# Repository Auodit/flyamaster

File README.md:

# 🚁 FLYAMASTER 飞控项目

> ⚠️ **版权警告 / COPYRIGHT WARNING** ⚠️
>
> **本项目受版权保护，严格保留所有权利！**
>
> 🚫 **禁止** 未经授权的复制、修改、分发、商用
> 🚫 **禁止** Fork、Clone、Download 本仓库
> 🚫 **禁止** 转载、引用本项目任何内容
>
> 违者将依法追究法律责任！详见 [LICENSE](LICENSE)
>
> ---
>
> **This project is protected by copyright. All rights strictly reserved!**
>
> 🚫 **PROHIBITED**: Unauthorized copying, modification, distribution, commercial use
> 🚫 **PROHIBITED**: Fork, Clone, Download this repository
> 🚫 **PROHIBITED**: Repost or cite any content from this project
>
> Violators will be prosecuted! See [LICENSE](LICENSE)

---

**项目名称**: FLYAMASTER - F405 Mini 高性能穿越机飞控
**版本**: v2.4.0
**最后更新**: 2026-01-23
**状态**: 🟢 开发中 (软件完成，硬件设计完成，等待验证)
**作者**: LI
**助手**: Doro *(Desktop Pet / 桌面宠物)*

---

## 📖 项目简介

FLYAMASTER 是一款基于 **STM32F405RGT6** 的高性能、开源、易扩展的四轴飞行控制器。

### 🌟 项目由来

> *"每个飞手心中都有一个造飞控的梦。"*

这个项目源于我对无人机的热爱。从第一次看到穿越机在空中翻滚、俯冲的那一刻起，我就被这种自由飞翔的感觉深深吸引。作为一名嵌入式开发者，我不满足于仅仅使用现成的飞控，而是想要**从零开始**，亲手打造一款属于自己的飞行控制器。

这不仅仅是一个技术项目，更是一段探索之旅——从最初的 Mahony 姿态解算调试，到 PID 参数的反复调优；从 DMA 通道冲突的抓狂，到最终看到四轴稳稳悬停的那一刻的成就感。每一行代码、每一条 PCB 走线，都凝聚着对飞行的热爱和对技术的追求。

**FLYAMASTER** = **FLY** (飞行) + **A** (一个) + **MASTER** (大师) —— 愿每一位使用者都能成为飞行大师！

### 🎯 多固件支持

本硬件设计兼容多种主流开源飞控固件：

| 固件 | 适用场景 | 支持状态 |
|------|----------|----------|
| **INAV** | 固定翼 / 长航时无人机 / GPS 导航 | ✅ 完全兼容 |
| **Betaflight** | 穿越机 / 竞速无人机 / 花飞 | ✅ 完全兼容 |
| **ArduPilot** | 专业航拍 / 测绘 / 自主任务 | ✅ 完全兼容 |
| **FLYAMASTER (自研)** | 学习研究 / 定制开发 | ✅ 原生支持 |

> 💡 **提示**: 硬件引脚分配遵循 Betaflight 标准，可直接使用 Betaflight Configurator 进行配置。
> 对于 INAV 和 ArduPilot，需要创建对应的 Target 定义文件。

### 核心特性

- **高性能 MCU**: STM32F405RGT6 (168MHz, 1MB Flash, 192KB RAM)
- **多固件兼容**: 支持 INAV / Betaflight / ArduPilot / 自研固件
- **宽电压输入**: 支持 **2S-9S 电池** (4.5V-40V)，兼容各类电调
- **板载 OSD**: AT7456E 视频叠加芯片，实时显示飞行数据
- **实时操作系统**: FreeRTOS CMSIS_V2 (自研固件)
- **姿态解算**: Mahony 互补滤波 (500Hz)
- **控制算法**: 串级 PID (角度环 + 角速度环)
- **传感器融合**: IMU + 气压计 + 磁力计 + GPS + 光流
- **遥控接收**: ELRS/CRSF 协议 (420kbps, 双向遥测)
- **黑匣子**: W25Q128 Flash 日志记录 (16MB)
- **状态指示**: 7 颗专业级 LED 飞行仪表盘
- **USB 反灌保护**: 肖特基二极管隔离，安全可靠

### 设计哲学

1. **控制回路隔离**: 姿态解算与 PID 控制拥有最高优先级
2. **DMA 满载策略**: 所有高吞吐量接口强制开启 DMA
3. **资源冲突零容忍**: 针对 F405 的 DMA 通道冲突采用硬件重映射方案

---

## 🧠 核心算法原理

### 姿态解算 - Mahony 互补滤波

飞控的"大脑"是姿态解算算法。我们采用 **Mahony 互补滤波器**，它巧妙地融合了陀螺仪和加速度计的数据：

```
                    ┌─────────────────────────────────────────┐
                    │         Mahony 互补滤波器               │
                    └─────────────────────────────────────────┘
                    
    陀螺仪 (高频响应)                      加速度计 (低频稳定)
         │                                      │
         ▼                                      ▼
    ┌─────────┐                           ┌─────────┐
    │ 角速度  │                           │ 重力向量│
    │ ω       │                           │ a       │
    └────┬────┘                           └────┬────┘
         │                                      │
         │    ┌──────────────────────────┐     │
         └───►│  四元数微分方程积分       │◄────┘
              │  q̇ = ½ q ⊗ ω_corrected   │
              └───────────┬──────────────┘
                          │
                          ▼
                    ┌─────────┐
                    │ 四元数 q │ ──► Roll, Pitch, Yaw
                    └─────────┘
```

**核心公式**:
- 误差估计: `e = a × v` (加速度计测量值与估计重力方向的叉积)
- PI 校正: `ω_corrected = ω_gyro + Kp·e + Ki·∫e·dt`
- 四元数更新: `q += ½·q⊗ω·dt`

### 串级 PID 控制

采用**角度环 + 角速度环**的串级结构，外环输出作为内环的设定值：

```
    目标角度 ──┬──► [角度环 PID] ──► 目标角速度 ──┬──► [角速度环 PID] ──► 电机输出
               │                                  │
    当前角度 ──┘                    当前角速度 ──┘
```

**为什么用串级？**
- 外环 (角度环): 响应慢但稳定，负责"往哪飞"
- 内环 (角速度环): 响应快，负责"怎么飞"
- 两环配合，既稳定又灵敏

### 电机混控 - Airmode 算法

X 型机架的混控公式：
```
M1 (右前) = Throttle - Roll - Pitch - Yaw
M2 (左后) = Throttle + Roll + Pitch - Yaw
M3 (左前) = Throttle + Roll - Pitch + Yaw
M4 (右后) = Throttle - Roll + Pitch + Yaw
```

**Airmode 的精髓**: 当电机输出超限时，整体平移油门中心，保证姿态控制差分不变——"姿态优先，油门让步"。

---

## ⚡ 电路设计亮点

### 宽电压电源架构 (2S-9S)

```
    电池 (4.5-40V) ──► SY8303 DCDC ──► 5V/3A ──► RT9193 LDO ──► 3.3V/500mA
         │                  │                         │
         │                  ├──► USB 5V (带反灌保护)   ├──► MCU
         │                  ├──► 蜂鸣器               ├──► 传感器
         │                  └──► 外设接口             └──► Flash/OSD
         │
         ├──► 电机 (直接电池供电)
         └──► ADC 电压检测 (1:11 分压)
```

**为什么选 SY8303？**
- 输入范围 4.5-40V，覆盖 2S-9S 电池
- 效率高达 95%，发热小
- SOT-23-6 封装，体积小巧
- 价格仅 ¥0.8，性价比极高

### USB 反灌保护

**问题**: 电池供电时，5V 会通过 USB 反灌到电脑，导致 MCU 误判 USB 已连接。

**解决方案**: 肖特基二极管 (SS14) 隔离 + PB9 检测引脚

```
    USB VBUS ──┬──[SS14 二极管]──► +5V_USB
               │
               └──[10kΩ]──► PB9 (USB_DETECT, Pull-down)
```

### 7 颗 LED 专业飞行仪表盘

| 分组 | LED | 颜色 | 功能 |
|:---|:---|:---|:---|
| 核心系统 | LED_SYS | 蓝 | 系统心跳 (闪烁=待机, 常亮=已解锁) |
| 核心系统 | LED_ERR | 红 | 警告/错误 (快闪=传感器故障) |
| 导航链路 | LED_GPS | 绿 | GPS 状态 (闪烁=搜星, 常亮=3D Fix) |
| 导航链路 | LED_RX | 黄 | 遥控信号 (常亮=正常, 灭=Failsafe) |
| 飞行任务 | LED_MODE | 白 | 飞行模式指示 |
| 飞行任务 | LED_LOG | 橙 | 黑匣子记录状态 |
| 飞行任务 | LED_VTX | 青 | 图传状态 |

---

## 🔧 问题发现与解决

开发过程中遇到了不少"坑"，这里记录一些典型问题和解决方案：

### 问题 1: DMA 通道冲突

**现象**: WS2812 RGB 灯和 SBUS 接收机同时工作时，数据错乱。

**原因**: STM32F4 的 DMA 通道是硬件绑定的，TIM3_CH4 和 UART4_RX 共用 DMA1_Stream2。

**解决**: 将 WS2812 从 TIM3_CH4 (PB1) 迁移到 TIM1_CH1 (PA8)，使用 DMA2 通道，彻底隔离。

### 问题 2: I2C 总线竞争

**现象**: 多任务环境下，MPU6050 和 SPL06 偶发读取失败。

**原因**: 两个任务同时访问 I2C1 总线，导致冲突。

**解决**: 引入 FreeRTOS 互斥锁 (`i2c1MutexHandle`)，所有 I2C 操作前加锁，操作后解锁。

### 问题 3: Failsafe 油门被覆盖 (严重!)

**现象**: 失控保护触发后，飞机不下降反而继续按遥控器油门飞行。

**原因**: 代码中先设置 `throttle = FAILSAFE_DESCENT_THROTTLE`，后又被 `throttle = SBUS_GetThrottle()` 覆盖。

**解决**: 在读取遥控器油门前检查 Failsafe 状态，Failsafe 期间跳过遥控器输入。

### 问题 4: 偏航角漂移

**现象**: 飞机静止时，Yaw 角缓慢漂移。

**原因**: 仅使用 6 轴 IMU (加速度计+陀螺仪)，无法校正偏航。

**解决**: 集成 QMC5883L 磁力计，升级为 9 轴 AHRS，利用地磁场校正偏航。

### 问题 5: 高频 printf 导致控制抖动

**现象**: 在 500Hz 的 IMU 任务中加 printf 调试，飞机开始抖动。

**原因**: printf 是阻塞式的，每次调用耗时 1-2ms，严重影响控制回路。

**解决**: 开发 RingBuffer 异步日志系统，`Log_Printf()` 仅需 <10us，数据通过 DMA 后台发送。

---

## 🛠️ 技术栈

| 类别 | 技术选型 | 说明 |
|------|----------|------|
| **MCU** | STM32F405RGT6 | ARM Cortex-M4F @ 168MHz |
| **RTOS** | FreeRTOS | CMSIS_V2 接口 |
| **IDE** | Keil MDK-ARM | ARM Compiler 6 |
| **配置工具** | STM32CubeMX | HAL 库生成 |
| **EDA** | KiCad 9.0 | PCB 设计 |
| **调试** | 匿名上位机 V7 | 实时数据可视化 |

---

## 📐 硬件设计

### PCB 渲染图

| 正面 (Top) | 反面 (Bottom) |
|:---:|:---:|
|  |  |

### 原理图

📄 **原理图 PDF**: [Hardware/zero star/zero star.pdf](Hardware/zero%20star/zero%20star.pdf)

### 主要芯片

| 芯片 | 功能 | 接口 |
|------|------|------|
| STM32F405RGT6 | 主控 MCU | - |
| MPU6050 | 6轴 IMU | I2C1 (0x68) |
| SPL06-001 | 气压计 | I2C1 (0x76) |
| QMC5883L | 磁力计 | I2C1 (0x0D) |
| W25Q128 | 16MB Flash | SPI1 |
| AT7456E | OSD 视频叠加 | SPI1 |
| SY8303 | DCDC 5V/3A (2S-9S 输入) | - |
| RT9193-33 | LDO 3.3V/500mA | - |

### 接口定义

| 接口 | 引脚 | 功能 | 波特率 |
|------|------|------|--------|
| J1 | USB-C | 固件升级/调参 | CDC |
| J2 | PA2/PA3 | GPS 模块 | 115200 |
| J3 | PA9/PA10 | K210 上位机 | 921600 |
| J4 | PC6-PC9 | 4-in-1 ESC | PWM 400Hz |
| J5 | PC12/PD2 | 光流模块 | 115200 |
| J6 | PC10/PC11 | VTX SmartAudio | 115200  |
| J22 | PB10/PB11 | ELRS 接收机 | 420000 (CRSF) |

---

## 📚 文档索引

| 编号 | 文档名称 | 说明 | 链接 |
|------|----------|------|------|
| 00 | README.md | 项目总览与索引 (本文档) | - |
| 01 | 01_definitions.md | 命名规范与接口定义 | [查看](plans/01_definitions.md) |
| 02 | 02_project_roadmap.md | 项目路线图与待办事项 | [查看](plans/02_project_roadmap.md) |
| 03 | 03_issue_tracker.md | 问题追踪日志 (Bug/Risk) | [查看](plans/03_issue_tracker.md) |
| 04 | 04_algo_design.md | 算法设计与优化记录 | [查看](plans/04_algo_design.md) |
| 05 | 05_changelog.md | 版本更新日志 | [查看](plans/05_changelog.md) |
| 06 | 06_operation_guide.md | 操作指南与环境搭建 | [查看](plans/06_operation_guide.md) |
| 07 | 07_research_and_ideas.md | 调研分析与创意池 | [查看](plans/07_research_and_ideas.md) |
| 08 | 08_hardware_design.md | 硬件架构与 PCB 设计 | [查看](plans/08_hardware_design.md) |

---

## 🚀 快速开始

### 1. 环境准备

```bash
# 必需软件
- Keil MDK-ARM v5.38+
- STM32CubeMX v6.10+
- ST-Link 驱动
```

### 2. 编译项目

1. 打开 `FLYAMASTER/MDK-ARM/FLYAMASTER.uvprojx`
2. 点击 `Build` (F7) 编译
3. 点击 `Download` (F8) 烧录

### 3. 调试连接

- **SWD 接口**: PA13 (SWDIO), PA14 (SWCLK)
- **USB 虚拟串口**: PA11/PA12 (CDC)
- **匿名上位机**: USART1 (PA9/PA10) @ 921600 baud

---

## 📁 目录结构

```
FLYAMASTER/
├── 3D/                      # 3D 模型文件
├── FLYAMASTER/              # 固件源代码
│   ├── Core/
│   │   ├── Inc/             # 头文件
│   │   │   ├── mpu6050.h    # IMU 驱动
│   │   │   ├── mahony.h     # 姿态解算
│   │   │   ├── pid.h        # PID 控制器
│   │   │   ├── motor.h      # 电机混控
│   │   │   ├── sbus.h       # CRSF 接收
│   │   │   ├── gps.h        # GPS 解析
│   │   │   ├── at7456e.h    # OSD 驱动
│   │   │   └── ...
│   │   └── Src/             # 源文件
│   │       ├── freertos.c   # RTOS 任务
│   │       ├── mpu6050.c    # IMU 驱动实现
│   │       ├── mahony.c     # Mahony 滤波
│   │       ├── pid.c        # PID 算法
│   │       ├── motor.c      # 电机控制
│   │       └── ...
│   └── MDK-ARM/             # Keil 工程
│       ├── FLYAMASTER.uvprojx
│       └── ...
├── Hardware/                # 硬件设计
│   └── zero star/           # KiCad 工程
│       ├── zero star.kicad_sch    # 原理图
│       ├── zero star.kicad_pcb    # PCB
│       └── zero star.pdf          # 原理图 PDF
├── plans/                   # 项目文档
│   ├── README.md            # 文档索引
│   ├── 01_definitions.md    # 接口定义
│   ├── 02_project_roadmap.md # 路线图
│   ├── 03_issue_tracker.md  # 问题追踪
│   ├── 04_algo_design.md    # 算法设计
│   ├── 05_changelog.md      # 更新日志
│   ├── 06_operation_guide.md # 操作指南
│   ├── 07_research_and_ideas.md # 调研分析
│   ├── 08_hardware_design.md # 硬件设计
│   └── archive/             # 废弃文档归档
├── .gitignore               # Git 忽略规则
└── LICENSE                  # 版权声明
```

---

## 🎯 项目状态

### ✅ 已完成

- [x] 硬件驱动 (IMU, PWM, CRSF, GPS, OSD)
- [x] 姿态解算 (Mahony 互补滤波)
- [x] 姿态控制 (串级 PID)
- [x] 定高控制 (气压计 PID)
- [x] GPS 定点 (位置环 PID)
- [x] OSD 显示 (AT7456E)
- [x] 匿名上位机协议 (V7)
- [x] 硬件原理图设计 (KiCad)
- [x] 7 颗 LED 状态指示系统
- [x] USB 插入检测 (反灌保护)

### 🚧 进行中

- [ ] PCB 布局优化
- [ ] 打样验证

### 📋 计划中

- [ ] EKF 状态估计 (可选)
- [ ] 航点飞行
- [ ] 自动返航 (RTH)

---

## 👥 贡献者

- **LI** - 项目作者 & 核心开发者
- **Doro** *(Desktop Pet / 桌面宠物)* - AI 助手 & 文档撰写

---

## ⚖️ 版权声明

```
================================================================================
                    FLYAMASTER 飞控项目 - 版权声明
================================================================================

版权所有 (C) 2026 FLYAMASTER 项目组
Copyright (C) 2026 FLYAMASTER Project Team

                       严格保留所有权利
                  ALL RIGHTS STRICTLY RESERVED

未经版权所有者明确书面授权，严禁：
1. 复制、下载、存储本项目的任何部分
2. 修改、改编、翻译本项目的任何内容
3. 分发、传播、共享本项目的任何文件
4. 将本项目用于任何商业目的
5. 基于本项目创建衍生作品
6. 对本项目进行逆向工程
7. 在任何平台转载、引用本项目内容

任何未经授权的使用将被视为侵权，版权所有者保留追究法律责任的权利。

详见 LICENSE 文件
================================================================================
```

---

## 🙏 致谢

感谢开源社区的前辈们，特别是：
- **Betaflight** / **INAV** / **ArduPilot** 项目，提供了宝贵的参考
- **Mahony** 和 **Madgwick** 的姿态解算算法论文
- **立创开源硬件平台**，提供了电源方案参考
- 所有在 GitHub Issues 中提供反馈的朋友们

---

**文档版本**: v2.4.0
**最后更新**: 2026-01-23
**作者**: LI | **助手**: Doro

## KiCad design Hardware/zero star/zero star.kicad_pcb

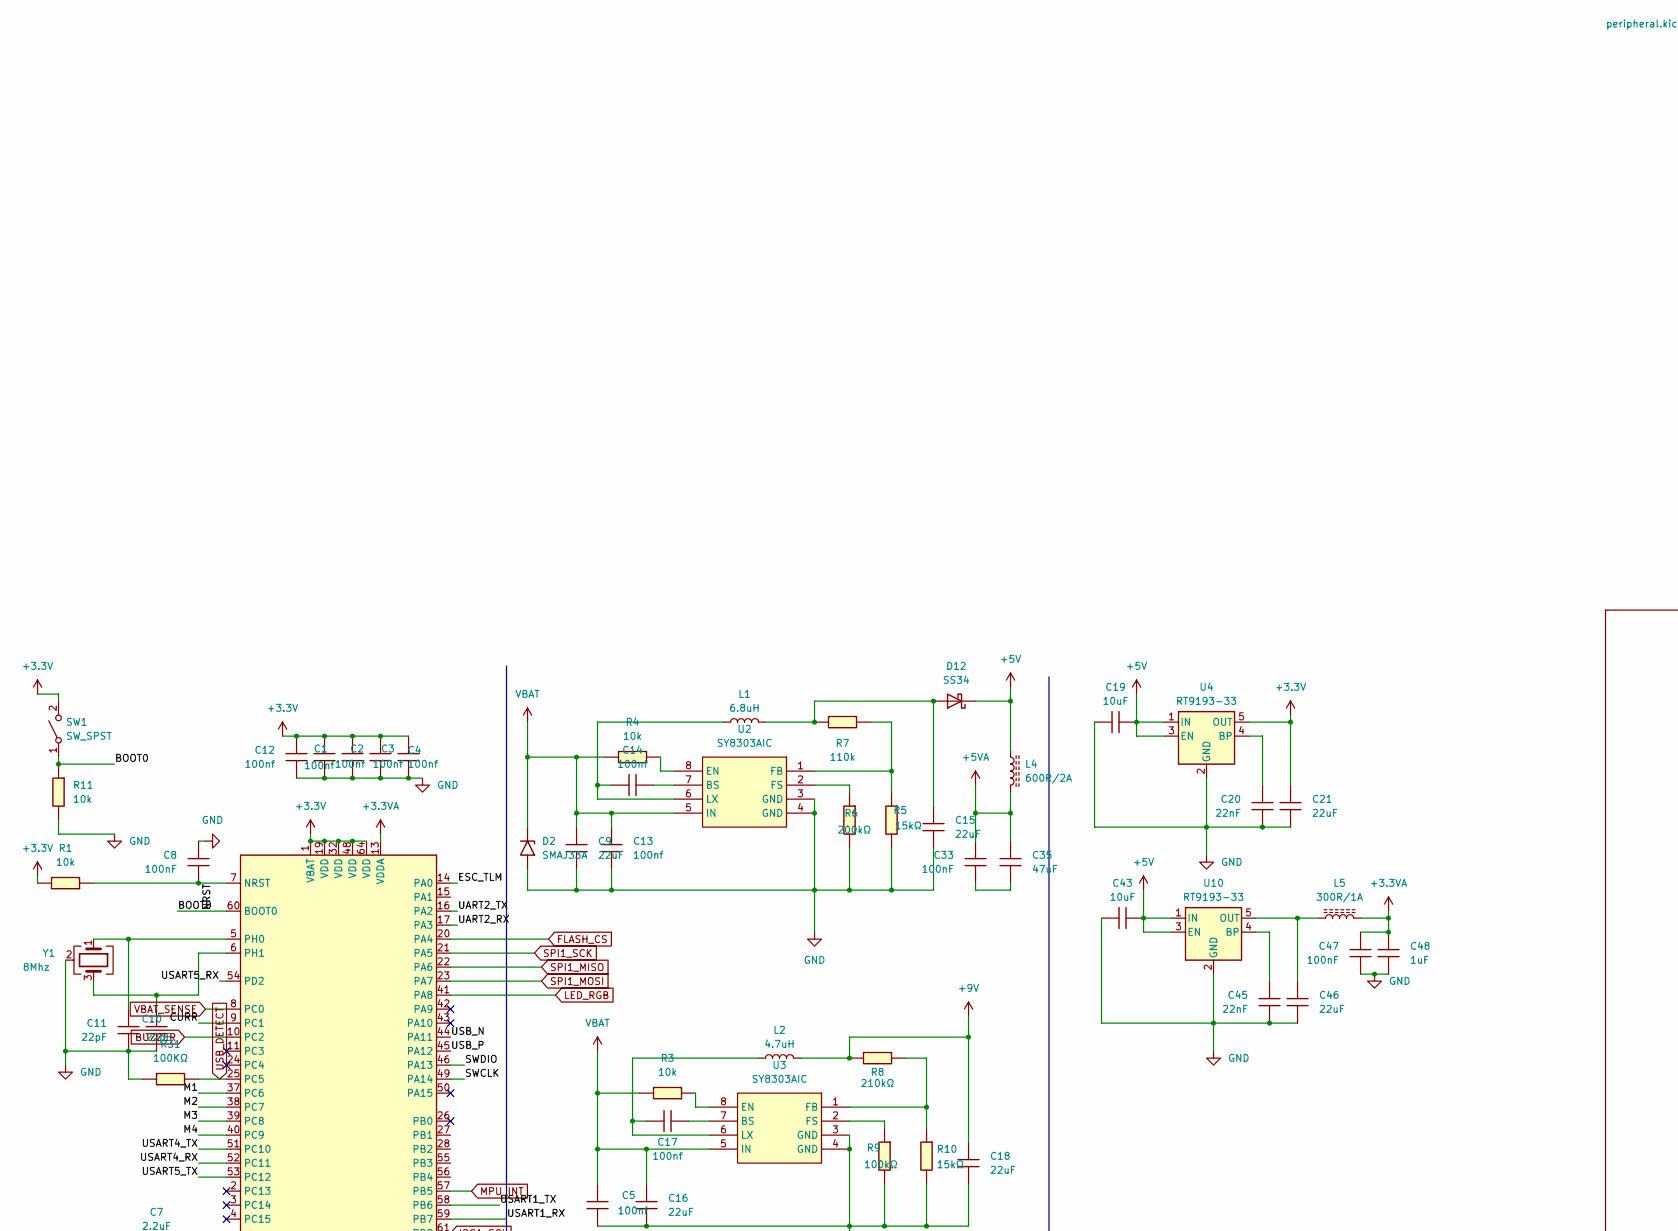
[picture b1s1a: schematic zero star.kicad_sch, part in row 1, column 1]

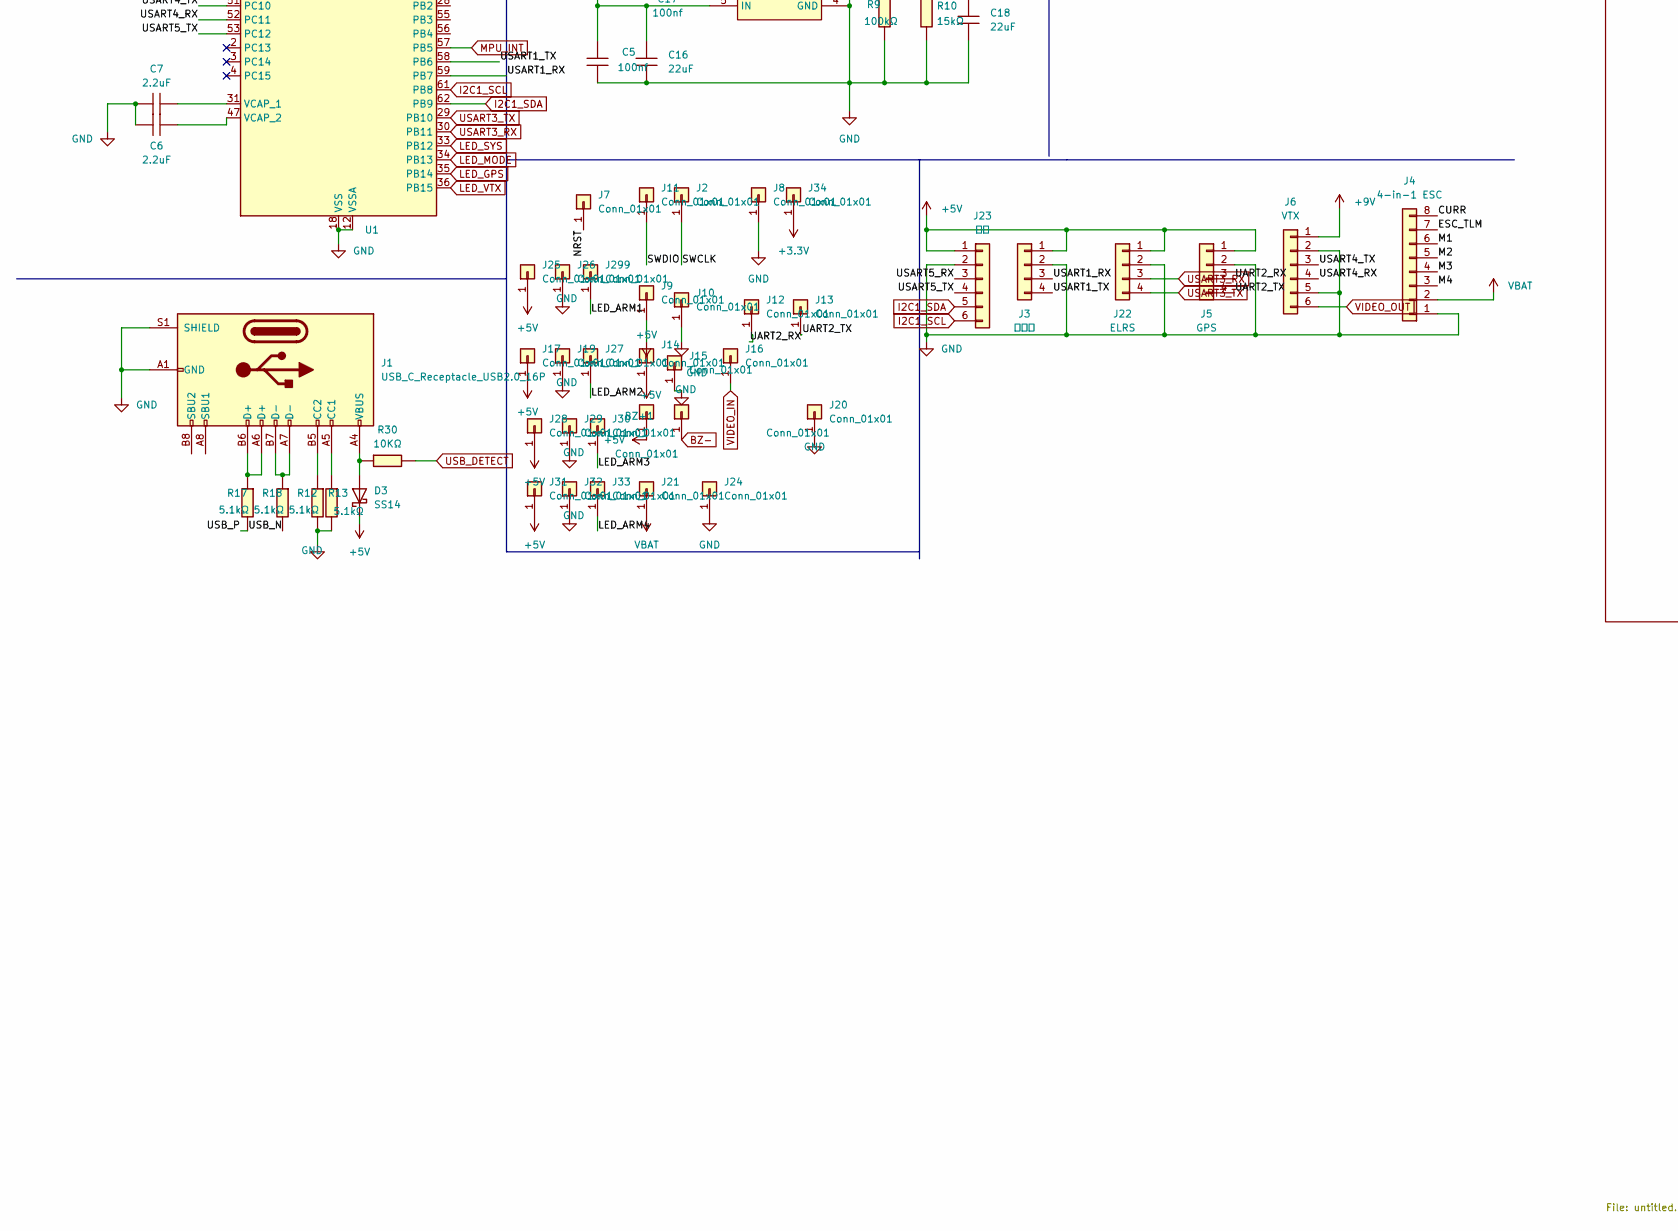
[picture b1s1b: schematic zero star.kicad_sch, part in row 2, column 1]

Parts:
BZ+1: Conn_01x01; SolderWirePad_1x01_SMD_1x2mm
C1, C2, C3, C4, C12, C13, C14, C16, C17: 100nf; C_0603
C5, C9, C15, C18, C21, C46: 22uF; C_0603
C6, C7: 2.2uF; C_0603
C8, C33, C47: 100nF; C_0603
C10, C11: 22pF; C_0603
C19, C43: 10uF; C_0603
C20, C45: 22nF; C_0603
C35: 47uF; C_0603
C48: 1uF; C_0603
D2: SMAJ33A; D_SMA
D3: SS14; D_SMA
D12: SS34; D_SOD-123
J1: USB_C_Receptacle_USB2.0_16P; USB_C_Receptacle_HRO_TYPE-C-31-M-12
J2, J7, J8, J9, J10, J11, J12, J13, J14, J15, J16, J17, J18, J19, J20, J21, J24, J25, J26, J27, J28, J29, J30, J31, J32, J33, J34, J299: Conn_01x01; SolderWirePad_1x01_SMD_1x2mm
J3: 上位机; JST_SH_SM04B-SRSS-TB_1x04-1MP_P1.00mm_Horizontal; Part Number 1-0401FBV0T
J4: 4-in-1 ESC; JST_SH_SM08B-SRSS-TB_1x08-1MP_P1.00mm_Horizontal
J5: GPS; JST_SH_SM04B-SRSS-TB_1x04-1MP_P1.00mm_Horizontal; Part Number 1-0401FBV0T
J6: VTX; JST_SH_SM06B-SRSS-TB_1x06-1MP_P1.00mm_Horizontal; Part Number 1-0601FBV0T
J22: ELRS; JST_SH_SM04B-SRSS-TB_1x04-1MP_P1.00mm_Horizontal; Part Number 1-0401FBV0T
J23: 光流; JST_SH_SM06B-SRSS-TB_1x06-1MP_P1.00mm_Horizontal; Part Number 1-0601FBV0T
L1: 6.8uH; L_Bourns-SRN4018
L2: 4.7uH; L_Bourns-SRN4018
L4: 600R/2A; L_0805_2012Metric_Pad1.05x1.20mm_HandSolder
L5: 300R/1A; L_0805_2012Metric_Pad1.05x1.20mm_HandSolder
R1, R3, R4, R11: 10k; R_0603
R5, R10: 15kΩ; R_0603
R6: 200kΩ; R_0603
R7: 110k; R_0603
R8: 210kΩ; R_0603
R9: 100kΩ; R_0603
R12, R13, R17, R18: 5.1kΩ; R_0603
R30: 10KΩ; R_0603
R31: 100KΩ; R_0603
SW1: SW_SPST; SW_SPST_B3U-3000P-B
U1: STM32F405RGTx; LQFP-64_10x10mm_P0.5mm
U2, U3: SY8303AIC; TSOT-23-8; LCSC Part C97054
U4, U10: RT9193-33; SOT-23-5
Y1: 8Mhz; Crystal_SMD_3225-4Pin_3.2x2.5mm

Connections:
+3.3V: C1.1, C2.1, C3.1, C4.1, C12.1, C21.1, J34.1, R1.1, SW1.2 (B), U1.1 (VBAT), U1.19 (VDD), U1.32 (VDD), U1.48 (VDD), U1.64 (VDD), U4.5 (OUT); also elsewhere on the board
+3.3VA: C47.1, C48.1, L5.2, U1.13 (VDDA); also elsewhere on the board
+5V: BZ+1.1, C19.1, C43.1, D3.1 (K), D12.1 (K), J3.1, J5.1, J9.1, J14.1, J17.1, J22.1, J23.1, J25.1, J28.1, J31.1, L4.1, U4.1 (IN), U4.3 (EN), U10.1 (IN), U10.3 (EN); also elsewhere on the board
+5VA: C33.1, C35.1, L4.2; also elsewhere on the board
+9V: C18.1, J6.1, L2.2, R8.2
/BOOT0: R11.2, SW1.1 (A), U1.60 (BOOT0)
/LED_ARM1: J299.1
/LED_ARM2: J27.1
/LED_ARM3: J30.1
/LED_ARM4: J33.1
/M1: J4.6, U1.37 (PC6)
/M2: J4.5, U1.38 (PC7)
/M3: J4.4, U1.39 (PC8)
/M4: J4.3, U1.40 (PC9)
/NRST: C8.2, J7.1, R1.2, U1.7 (NRST)
/SWCLK: J2.1, U1.49 (PA14)
/SWDIO: J11.1, U1.46 (PA13)
/UART2_RX: J5.3, J12.1, U1.17 (PA3)
/UART2_TX: J5.4, J13.1, U1.16 (PA2)
/USART1_RX: J3.3, U1.59 (PB7)
/USART1_TX: J3.4, U1.58 (PB6)
/USART4_RX: J6.4, U1.52 (PC11)
/USART4_TX: J6.3, U1.51 (PC10)
/USART5_RX: J23.3, U1.54 (PD2)
/USART5_TX: J23.4, U1.53 (PC12)
/USB_N: R18.1, U1.44 (PA11)
/USB_P: R17.1, U1.45 (PA12)
BUZZER: U1.10 (PC2); also elsewhere on the board
BZ-: J18.1; also elsewhere on the board
FLASH_CS: U1.24 (PC4); also elsewhere on the board
I2C1_SCL: J23.6, U1.61 (PB8); also elsewhere on the board
I2C1_SDA: J23.5, U1.62 (PB9); also elsewhere on the board
LED_GPS: U1.35 (PB14); also elsewhere on the board
LED_MODE: U1.34 (PB13); also elsewhere on the board
LED_RGB: U1.41 (PA8)
LED_SYS: U1.33 (PB12); also elsewhere on the board
LED_VTX: U1.36 (PB15); also elsewhere on the board
MPU_INT: U1.57 (PB5); also elsewhere on the board
unnamed: D3.2 (A), J1.A4 (VBUS), J1.A9 (VBUS), J1.B4 (VBUS), J1.B9 (VBUS), R30.2
unnamed: C15.1, D12.2 (A), L1.2, R7.2
unnamed: J1.A5 (CC1), R13.2
unnamed: J1.A6 (D+), J1.B6 (D+), R17.2
unnamed: J1.A7 (D-), J1.B7 (D-), R18.2
unnamed: J1.B5 (CC2), R12.2
unnamed: C11.1, U1.5 (PH0), Y1.1
unnamed: C10.1, U1.6 (PH1), Y1.3
unnamed: C7.1, U1.31 (VCAP_1)
unnamed: C6.1, U1.47 (VCAP_2)
unnamed: C14.2, U2.7 (BS)
unnamed: R4.2, U2.8 (EN)
unnamed: R5.2, R7.1, U2.1 (FB)
unnamed: R6.2, U2.2 (FS)
unnamed: C14.1, L1.1, U2.6 (LX)
unnamed: C17.2, U3.7 (BS)
unnamed: R3.2, U3.8 (EN)
unnamed: R8.1, R10.2, U3.1 (FB)
unnamed: R9.2, U3.2 (FS)
unnamed: C17.1, L2.1, U3.6 (LX)
unnamed: C20.1, U4.4 (BP)
unnamed: C45.1, U10.4 (BP)
unnamed: C46.1, L5.1, U10.5 (OUT)
SPI1_MISO: U1.22 (PA6); also elsewhere on the board
SPI1_MOSI: U1.23 (PA7); also elsewhere on the board
SPI1_SCK: U1.21 (PA5); also elsewhere on the board
USART3_RX: J22.3, U1.30 (PB11)
USART3_TX: J22.4, U1.29 (PB10)
USB_DETECT: R30.1, R31.1, U1.25 (PC5)
VBAT: C5.1, C9.1, C13.1, C16.1, D2.1 (A1), J4.2, J21.1, R3.1, R4.1, U2.5 (IN), U3.5 (IN); also elsewhere on the board
VBAT_SENSE: U1.8 (PC0); also elsewhere on the board
VIDEO_IN: J16.1; also elsewhere on the board
VIDEO_OUT: J6.6; also elsewhere on the board

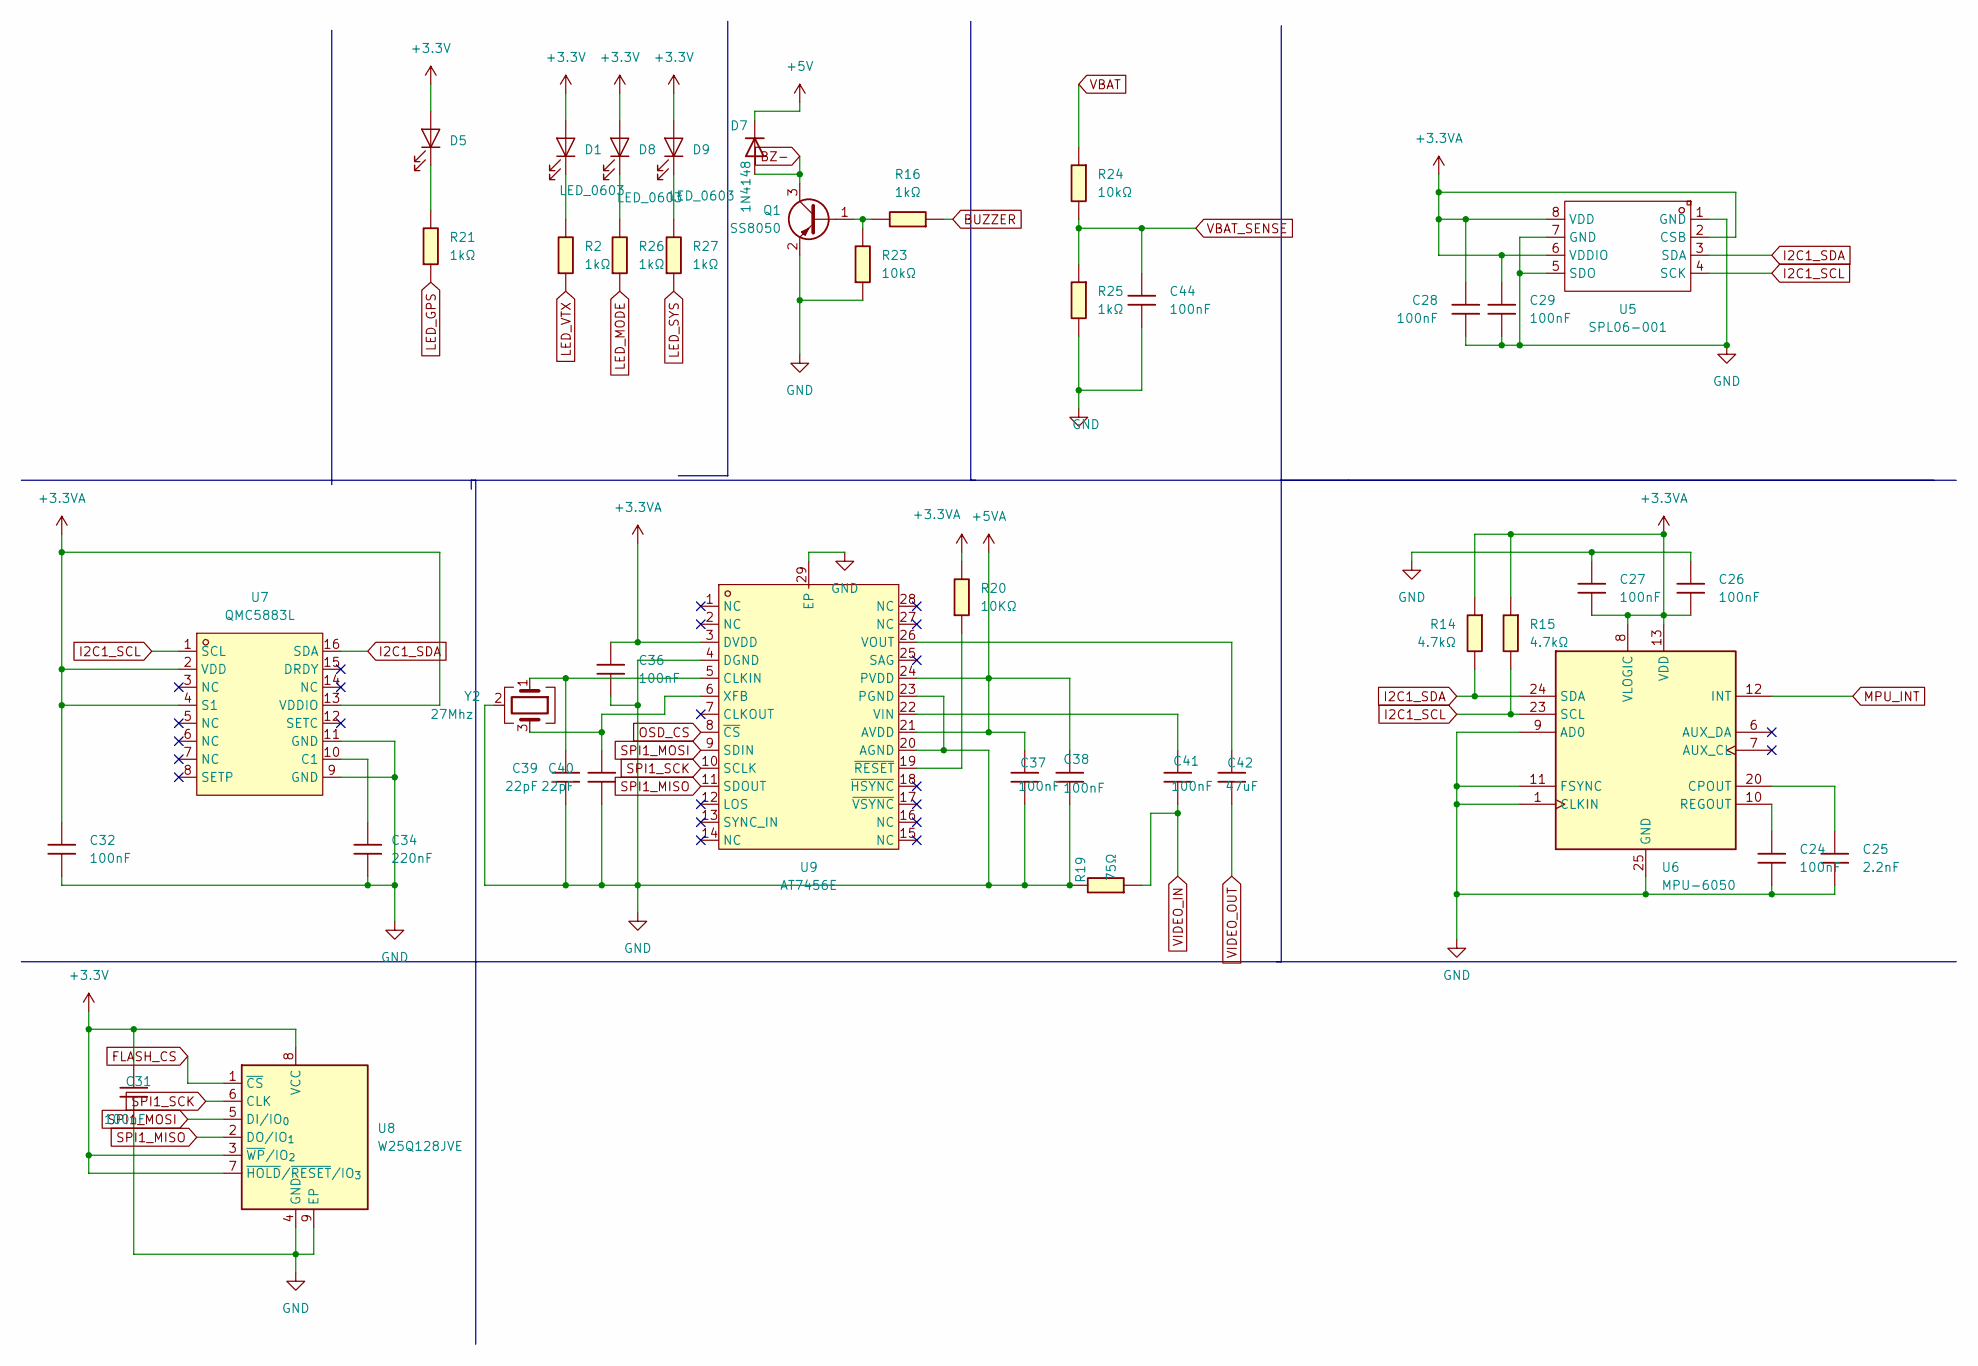
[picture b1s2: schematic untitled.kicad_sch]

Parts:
C24, C26, C27, C28, C29, C31, C32, C36, C37, C38, C41, C44: 100nF; C_0603
C25: 2.2nF; C_0603
C34: 220nF; C_0603
C39, C40: 22pF; C_0603
C42: 47uF; C_0603
D1, D5, D8, D9: LED_0603
D7: 1N4148; D_SOD-123
Q1: SS8050; SOT-23
R2, R16, R21, R25, R26, R27: 1kΩ; R_0603
R14, R15: 4.7kΩ; R_0603
R19: 75Ω; R_0603
R20: 10KΩ; R_0603
R23, R24: 10kΩ; R_0603
U5: SPL06-001; SENSOR-SMD_SPL06-001; LCSC Part C2684428
U6: MPU-6050; QFN-24-1EP_4x4mm_P0.5mm_EP2.6x2.6mm_ThermalVias
U7: QMC5883L; LGA-16_L3.0-W3.0-P0.50-BL_SQ; LCSC Part C976032
U8: W25Q128JVE; WSON-8-1EP_8x6mm_P1.27mm_EP3.4x4.3mm
U9: AT7456E; TSSOP-28_L9.7-W4.4-P0.65-LS6.4-BL-EP-2; LCSC Part C82351
Y2: 27Mhz; Crystal_SMD_3225-4Pin_3.2x2.5mm

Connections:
+3.3V: C31.1, D1.2 (A), D5.2 (A), D8.2 (A), D9.2 (A), U8.3 (~WP/IO_{2}), U8.7 (~HOLD/~RESET/IO_{3}), U8.8 (VCC); also elsewhere on the board
+3.3VA: C26.2, C27.2, C28.1, C29.1, C32.1, C36.1, R14.2, R15.2, R20.1, U5.2 (CSB), U5.6 (VDDIO), U5.8 (VDD), U6.8 (VLOGIC), U6.13 (VDD), U7.2 (VDD), U7.4 (S1), U7.13 (VDDIO), U9.3 (DVDD); also elsewhere on the board
+5V: D7.1 (K); also elsewhere on the board
+5VA: C37.1, C38.1, U9.21 (AVDD), U9.24 (PVDD); also elsewhere on the board
BUZZER: R16.2; also elsewhere on the board
BZ-: D7.2 (A), Q1.3 (C); also elsewhere on the board
FLASH_CS: U8.1 (~CS); also elsewhere on the board
I2C1_SCL: R15.1, U5.4 (SCK), U6.23 (SCL), U7.1 (SCL); also elsewhere on the board
I2C1_SDA: R14.1, U5.3 (SDA), U6.24 (SDA), U7.16 (SDA); also elsewhere on the board
LED_GPS: R21.2; also elsewhere on the board
LED_MODE: R26.2; also elsewhere on the board
LED_SYS: R27.2; also elsewhere on the board
LED_VTX: R2.2; also elsewhere on the board
MPU_INT: U6.12 (INT); also elsewhere on the board
unnamed: D1.1 (K), R2.1
unnamed: D5.1 (K), R21.1
unnamed: D8.1 (K), R26.1
unnamed: D9.1 (K), R27.1
unnamed: Q1.1 (B), R16.1, R23.1
unnamed: C25.1, U6.20 (CPOUT)
unnamed: C24.1, U6.10 (REGOUT)
unnamed: C34.1, U7.10 (C1)
unnamed: C39.1, U9.5 (CLKIN), Y2.1
unnamed: C41.1, U9.22 (VIN)
unnamed: C42.1, U9.26 (VOUT)
unnamed: C40.1, U9.6 (XFB), Y2.3
unnamed: R20.2, U9.19 (~RESET)
SPI1_MISO: U8.2 (DO/IO_{1}), U9.11 (SDOUT); also elsewhere on the board
SPI1_MOSI: U8.5 (DI/IO_{0}), U9.9 (SDIN); also elsewhere on the board
SPI1_SCK: U8.6 (CLK), U9.10 (SCLK); also elsewhere on the board
VBAT: R24.2; also elsewhere on the board
VBAT_SENSE: C44.1, R24.1, R25.2; also elsewhere on the board
VIDEO_IN: C41.2, R19.2; also elsewhere on the board
VIDEO_OUT: C42.2; also elsewhere on the board

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
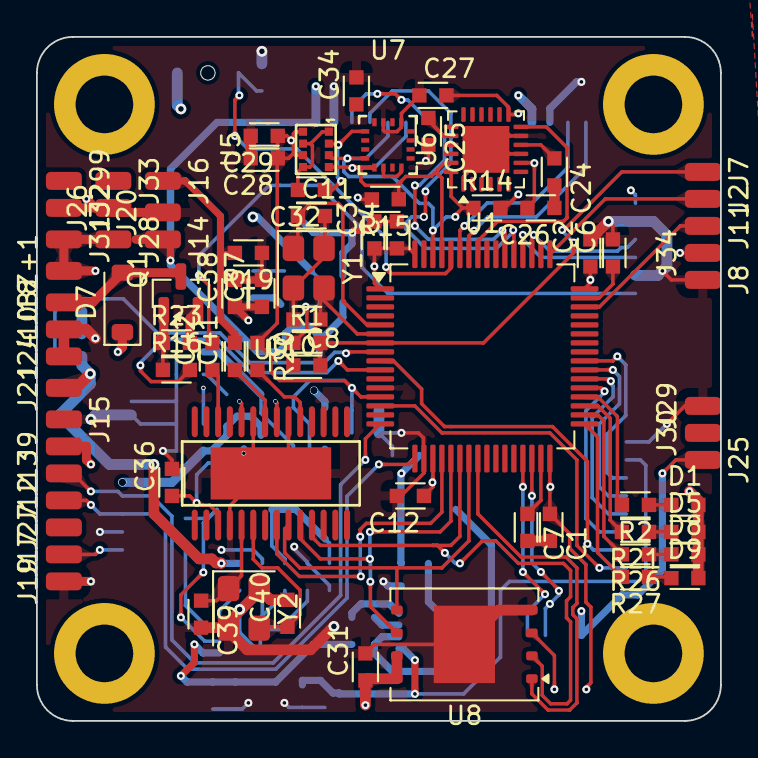
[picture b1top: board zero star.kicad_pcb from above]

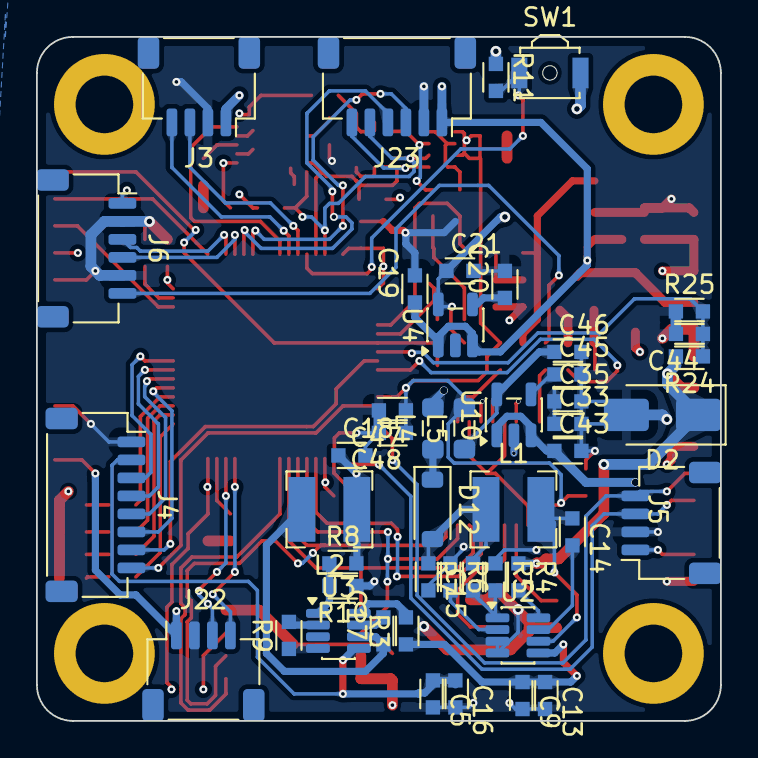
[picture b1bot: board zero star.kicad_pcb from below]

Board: 4 copper layers, 38.0 x 38.0 mm, 127 parts (47 on the bottom side), 75 nets.

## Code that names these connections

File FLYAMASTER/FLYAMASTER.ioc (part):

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Mcu.Name=STM32F405RGTx
Mcu.Package=LQFP64
Mcu.UserName=STM32F405RGTx
PA0-WKUP.GPIOParameters=GPIO_PuPd,GPIO_Label
PA0-WKUP.GPIO_Label=Power_Key
PA0-WKUP.GPIO_PuPd=GPIO_PULLDOWN
PA0-WKUP.Signal=GPIO_Input
PA11.Mode=Device_Only
PA11.Signal=USB_OTG_FS_DM
PA12.Mode=Device_Only
PA12.Signal=USB_OTG_FS_DP
PA13.Mode=Serial_Wire
PA13.Signal=SYS_JTMS-SWDIO
PA14.Mode=Serial_Wire
PA14.Signal=SYS_JTCK-SWCLK
PA2.Mode=Asynchronous
PA2.Signal=USART2_TX
PA3.Mode=Asynchronous
PA3.Signal=USART2_RX
PA4.GPIOParameters=GPIO_Speed,GPIO_Label
PA4.GPIO_Label=FLASH_CS
PA4.GPIO_Speed=GPIO_SPEED_FREQ_HIGH
PA4.Signal=GPIO_Output
PA5.Mode=Full_Duplex_Master
PA5.Signal=SPI1_SCK
PA6.Mode=Full_Duplex_Master
PA6.Signal=SPI1_MISO
PA7.Mode=Full_Duplex_Master
PA7.Signal=SPI1_MOSI
PA8.Signal=S_TIM1_CH1
PB0.GPIOParameters=GPIO_Speed
PB0.GPIO_Speed=GPIO_SPEED_FREQ_HIGH
PB0.Signal=GPIO_Output
PB10.GPIOParameters=GPIO_PuPd
PB10.GPIO_PuPd=GPIO_PULLUP
PB10.Mode=Asynchronous
PB10.Signal=USART3_TX
PB11.GPIOParameters=GPIO_PuPd
PB11.GPIO_PuPd=GPIO_PULLUP
PB11.Mode=Asynchronous
PB11.Signal=USART3_RX
PB12.Signal=GPIO_Output
PB13.GPIOParameters=PinState
PB13.PinState=GPIO_PIN_SET
PB13.Signal=GPIO_Output
PB14.GPIOParameters=PinState
PB14.PinState=GPIO_PIN_SET
PB14.Signal=GPIO_Output
PB15.GPIOParameters=PinState
PB15.PinState=GPIO_PIN_SET
PB15.Signal=GPIO_Output
PB5.GPIOParameters=GPIO_PuPd
PB5.GPIO_PuPd=GPIO_NOPULL
PB5.Signal=GPXTI5
PB6.Mode=Asynchronous
PB6.Signal=USART1_TX
PB7.Mode=Asynchronous
PB7.Signal=USART1_RX
PB8.Mode=I2C
PB8.Signal=I2C1_SCL
PB9.Mode=I2C
PB9.Signal=I2C1_SDA
PC0.Signal=ADCx_IN10
PC1.Signal=ADCx_IN11
PC10.Mode=Asynchronous
PC10.Signal=UART4_TX
PC11.Mode=Asynchronous
PC11.Signal=UART4_RX
PC12.GPIOParameters=GPIO_Label
PC12.GPIO_Label=Optical Flow
PC12.Mode=Asynchronous
PC12.Signal=UART5_TX
PC2.Signal=GPIO_Output
PC4.GPIOParameters=GPIO_Speed
PC4.GPIO_Speed=GPIO_SPEED_FREQ_HIGH
PC4.Signal=GPIO_Output
PC5.Signal=GPIO_Input
PC6.Signal=S_TIM8_CH1
PC7.Signal=S_TIM8_CH2
PC8.Signal=S_TIM8_CH3
PC9.Signal=S_TIM8_CH4
PD2.GPIOParameters=GPIO_Label
PD2.GPIO_Label=Optical Flow
PD2.Mode=Asynchronous
PD2.Signal=UART5_RX
PH0-OSC_IN.Mode=HSE-External-Oscillator
PH0-OSC_IN.Signal=RCC_OSC_IN
PH1-OSC_OUT.Mode=HSE-External-Oscillator
PH1-OSC_OUT.Signal=RCC_OSC_OUT
RCC.HSE_VALUE=8000000
RCC.SYSCLKFreq_VALUE=168000000
RCC.SYSCLKSource=RCC_SYSCLKSOURCE_PLLCLK
board=custom

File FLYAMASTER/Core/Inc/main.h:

/* USER CODE BEGIN Header */
/**
  ******************************************************************************
  * @file           : main.h
  * @brief          : Header for main.c file.
  *                   This file contains the common defines of the application.
  ******************************************************************************
  * @attention
  *
  * Copyright (c) 2026 STMicroelectronics.
  * All rights reserved.
  *
  * This software is licensed under terms that can be found in the LICENSE file
  * in the root directory of this software component.
  * If no LICENSE file comes with this software, it is provided AS-IS.
  *
  ******************************************************************************
  */
/* USER CODE END Header */

/* Define to prevent recursive inclusion -------------------------------------*/
#ifndef __MAIN_H
#define __MAIN_H

#ifdef __cplusplus
extern "C" {
#endif

/* Includes ------------------------------------------------------------------*/
#include "stm32f4xx_hal.h"

/* Private includes ----------------------------------------------------------*/
/* USER CODE BEGIN Includes */

/* USER CODE END Includes */

/* Exported types ------------------------------------------------------------*/
/* USER CODE BEGIN ET */

/* USER CODE END ET */

/* Exported constants --------------------------------------------------------*/
/* USER CODE BEGIN EC */

/* USER CODE END EC */

/* Exported macro ------------------------------------------------------------*/
/* USER CODE BEGIN EM */

/* USER CODE END EM */

/* Exported functions prototypes ---------------------------------------------*/
void Error_Handler(void);

/* USER CODE BEGIN EFP */

/* USER CODE END EFP */

/* Private defines -----------------------------------------------------------*/
#define Power_Key_Pin GPIO_PIN_0
#define Power_Key_GPIO_Port GPIOA
#define FLASH_CS_Pin GPIO_PIN_4
#define FLASH_CS_GPIO_Port GPIOA
#define Optical_Flow_Pin GPIO_PIN_12
#define Optical_Flow_GPIO_Port GPIOC
#define Optical_FlowD2_Pin GPIO_PIN_2
#define Optical_FlowD2_GPIO_Port GPIOD

/* USER CODE BEGIN Private defines */

/* SPI 片选引脚定义 (根据硬件设计文档 08_hardware_design.md v2.5.7) */
/* 注意: CubeMX 生成的 FLASH_CS 在 PA4，但设计文档要求:
 *   - PA4 = OSD_CS (AT7456E OSD 芯片)
 *   - PC4 = FLASH_CS (W25Q128 Flash)
 * 如果 PCB 按设计文档布线，需要在 CubeMX 中修正引脚标签
 */
#define OSD_CS_Pin GPIO_PIN_4
#define OSD_CS_GPIO_Port GPIOC

/* LED 引脚定义 (根据硬件设计文档 08_hardware_design.md) */
#define LED_BLUE_Pin GPIO_PIN_3
#define LED_BLUE_GPIO_Port GPIOC
#define LED_RED_Pin GPIO_PIN_4
#define LED_RED_GPIO_Port GPIOC

/* 蜂鸣器引脚定义 */
#define BUZZER_Pin GPIO_PIN_2
#define BUZZER_GPIO_Port GPIOC

/* 电源控制引脚定义 */
#define PWR_HOLD_Pin GPIO_PIN_1
#define PWR_HOLD_GPIO_Port GPIOC

/* USER CODE END Private defines */

#ifdef __cplusplus
}
#endif

#endif /* __MAIN_H */

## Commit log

2026-01-15 Add .kilocode to gitignore
2026-01-23 feat(hw): FLYAMASTER v2.4.0 硬件设计完成
2026-01-23 docs: 添加强版权声明 - 严格保留所有权利
2026-01-23 docs: 添加项目根目录 README.md (含原理图链接)
2026-01-23 docs: 添加多固件支持说明 (INAV/Betaflight/ArduPilot)
2026-01-23 docs: 更新贡献者信息
2026-01-23 docs: 添加 OSD 和 2S-9S 电调支持说明
2026-01-23 Update VTX SmartAudio baud rate to 115200
2026-01-23 update README.md.
2026-01-23 docs: 添加 PCB 渲染图 (正反面)
2026-01-23 docs: README 添加 PCB 渲染图展示
2026-01-23 update LICENSE.
2026-01-23 docs: README 润色 - 添加项目由来、算法原理、问题解决、作者信息
2026-01-25 HW v2.5.7: SPI CS pin swap, PCB layout v1, CubeMX update
